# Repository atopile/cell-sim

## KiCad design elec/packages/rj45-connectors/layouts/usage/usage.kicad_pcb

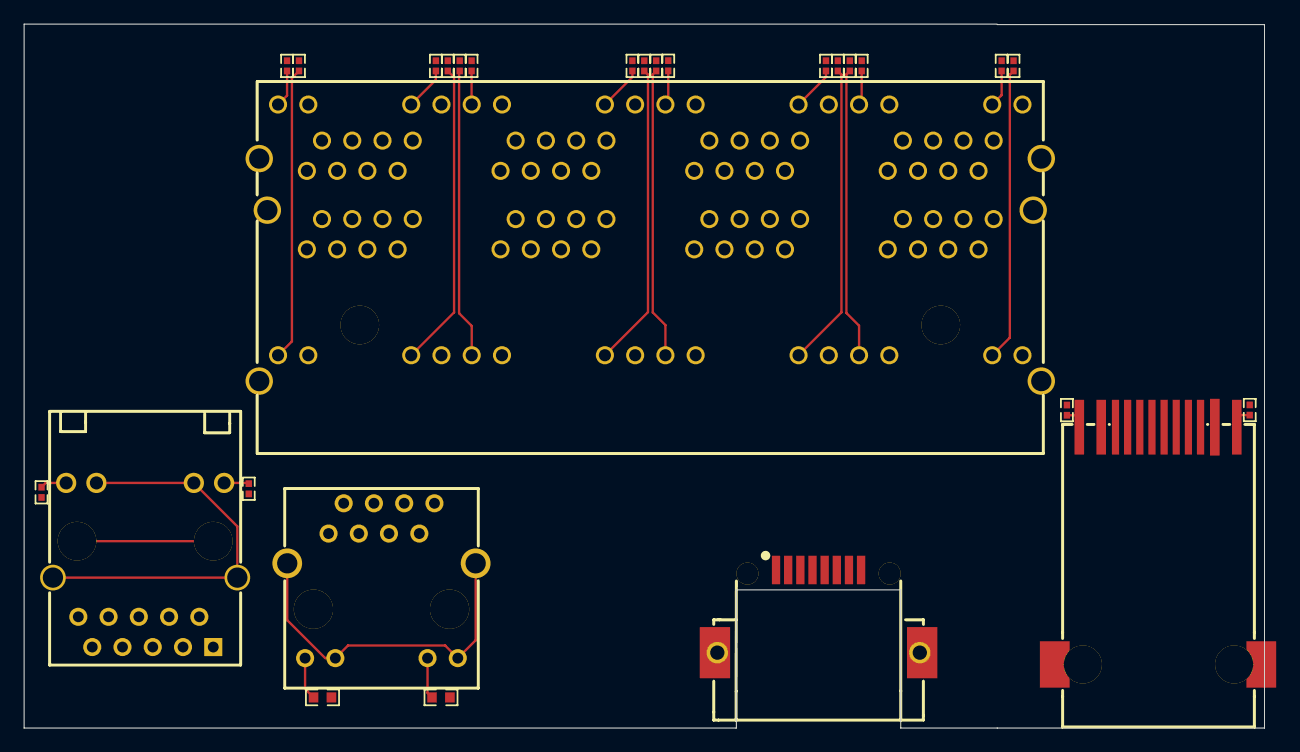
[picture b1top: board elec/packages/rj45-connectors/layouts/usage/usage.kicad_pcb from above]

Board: 2 copper layers, 104.1 x 59.1 mm, 27 parts (0 on the bottom side), 24 nets.

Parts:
R1, R2, R5, R6, R7, R8, R9, R10, R11, R12, R13, R14, R15, R16, R17, R18, R19, R20, R21, R22: 470Ω; R0402
R3, R4: 10kΩ; R0603
RJ1: RJ45-TH_HR911130A
RJ2: RJ45-SMD_BS-R250210
U1: RJ45-TH_R-RJ45S08P-C000
U2: RJ45-SMD_HC-RJ45-055-7_1
U3: RJ45-TH_HC-RJ45-059C-2X4-1

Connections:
10: R13.2, U3.10
11: R2.2, RJ1.11
12: R5.2, U3.12
14: R1.2, RJ1.14
22: R14.2, U3.22
24: R6.2, U3.24
34: R15.2, U3.34
36: R7.2, U3.36
46: R16.2, U3.46
48: R8.2, U3.48
57: R9.2, U3.57
59: R17.2, U3.59
69: R10.2, U3.69
71: R18.2, U3.71
81: R11.2, U3.81
83: R19.2, U3.83
93: R12.2, U3.93
95: R20.2, U3.95
CT: RJ2.3, RJ2.4
Gpos: R4.2, U1.11
L_LED_Gpos: R22.2, RJ2.12
R_LEDYpos: R21.2, RJ2.9
Ypos: R3.2, U1.9
lv: RJ1.12, RJ1.13, RJ1.SHIELD0, RJ1.SHIELD1, RJ2.8, RJ2.10, RJ2.11, RJ2.13, RJ2.14, U1.10, U1.12, U1.13, U1.14, U2.9, U2.10, U3.9, U3.11, U3.21, U3.23, U3.33, U3.35, U3.45, U3.47, U3.58, U3.60, U3.70, U3.72, U3.82, U3.84, U3.94, U3.96, U3.97, U3.98, U3.99, U3.100, U3.101, U3.102

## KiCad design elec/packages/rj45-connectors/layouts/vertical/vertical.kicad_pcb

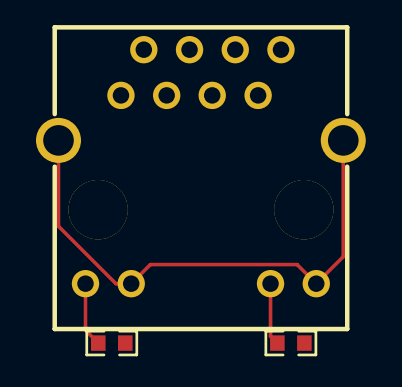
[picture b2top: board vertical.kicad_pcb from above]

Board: 2 copper layers, 3 parts (0 on the bottom side), 3 nets.

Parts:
R1, R2: 10kΩ; R0603
RJ1: RJ45-TH_R-RJ45S08P-C000

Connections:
Gpos: R2.2, RJ1.11
Ypos: R1.2, RJ1.9
lv: RJ1.10, RJ1.12, RJ1.13, RJ1.14

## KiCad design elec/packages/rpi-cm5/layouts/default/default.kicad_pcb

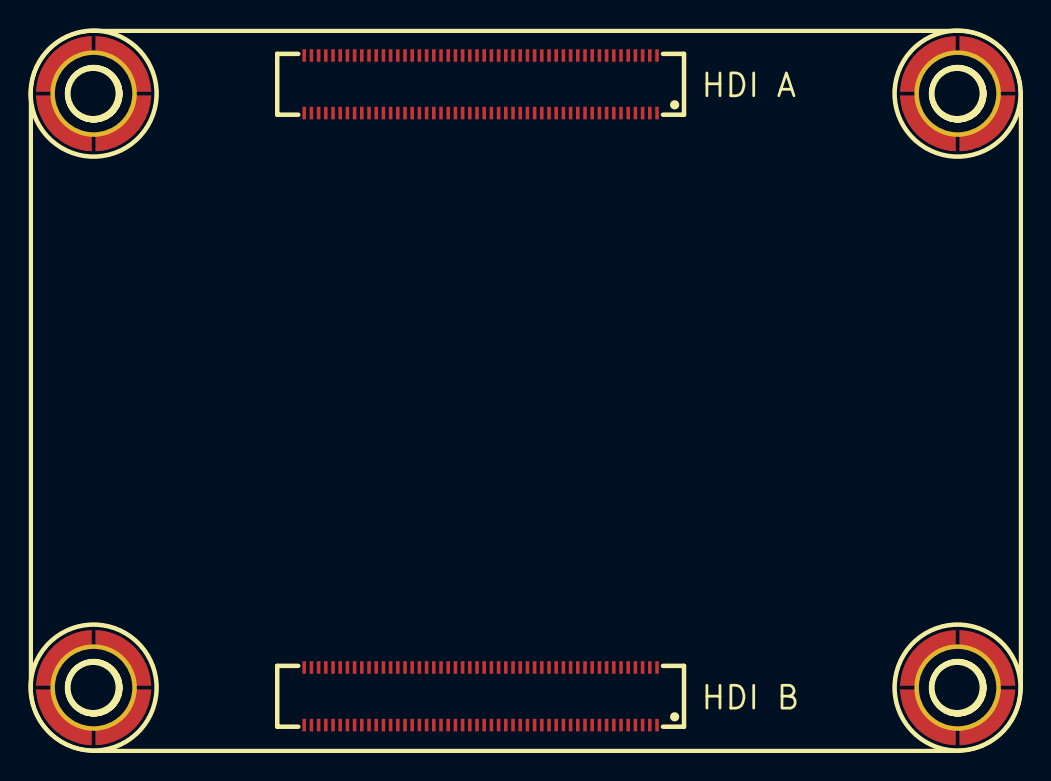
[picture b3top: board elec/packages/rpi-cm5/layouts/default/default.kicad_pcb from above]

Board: 4 copper layers, 7 parts (0 on the bottom side), 5 nets, no tracks yet.

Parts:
CN1, CN2: CONN-SMD_DF40C-100DS-0.4V-51
U1, U2, U3, U4: SMD_BD5.6-D4.1
U5: cm5

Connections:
lv: CN1.1, CN1.4, CN1.7, CN1.11, CN1.16, CN1.21, CN1.26, CN1.30, CN1.33, CN1.37, CN1.49, CN1.65, CN1.68, CN1.71, CN1.74, CN1.79, CN1.84, CN1.89, CN1.94, CN1.97, CN1.100, CN2.4, CN2.7, CN2.10, CN2.13, CN2.16, CN2.22, CN2.28, CN2.31, CN2.34, CN2.37, CN2.40, CN2.43, CN2.46, CN2.49, CN2.52, CN2.55, CN2.58, CN2.61, CN2.64, CN2.67, CN2.70, CN2.73, CN2.82, CN2.85, CN2.88, CN2.91, CN2.94, CN2.97
power_1v8-hv: CN1.44, CN1.45
power_3v3-hv: CN1.42, CN1.43
power_3v3-lv: U1.1, U1.2, U1.3, U1.4, U1.5, U2.1, U2.2, U2.3, U2.4, U2.5, U3.1, U3.2, U3.3, U3.4, U3.5, U4.1, U4.2, U4.3, U4.4, U4.5
power_5v-hv: CN1.57, CN1.58, CN1.59, CN1.60, CN1.61, CN1.62

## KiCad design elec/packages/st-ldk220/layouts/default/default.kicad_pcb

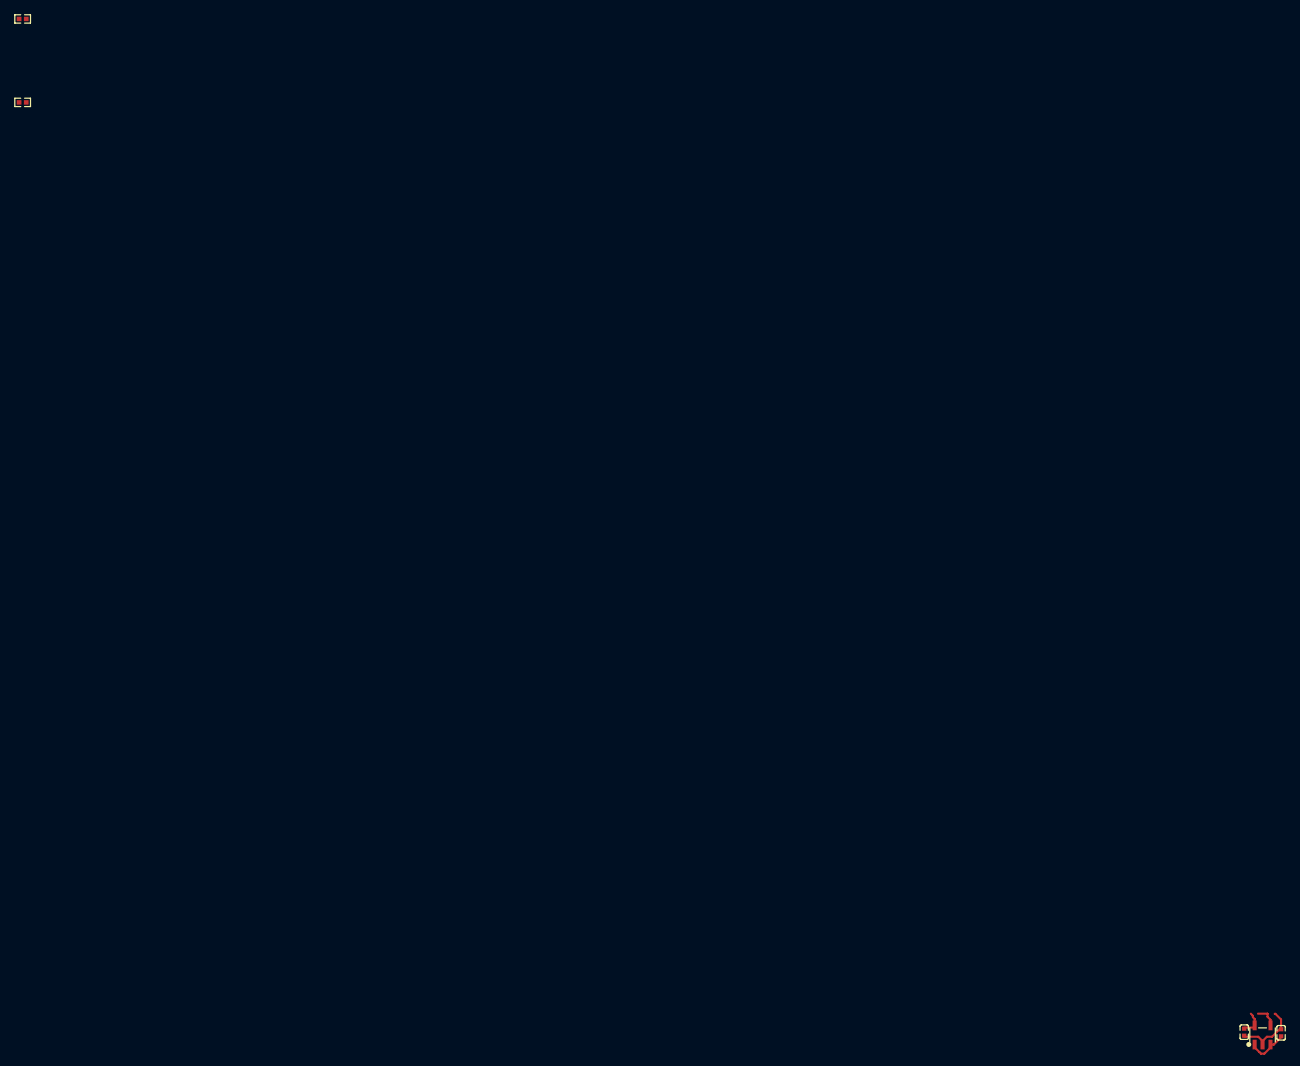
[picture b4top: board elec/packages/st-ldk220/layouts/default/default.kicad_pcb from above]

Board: 2 copper layers, 5 parts (0 on the bottom side), 5 nets.

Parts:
C1, C2: 1µF; C0402
R1, R2: 10kΩ; R0402
U1: SOT-23-5_L3.0-W1.7-P0.95-LS2.8-BL

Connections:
hv: C2.1, R1.1, U1.5
input_decoupling_capacitor-power-hv: C1.1, U1.1, U1.3
input_decoupling_capacitor-power-lv: C1.2, U1.2
lv: C2.2, R2.2
ref_out-hv: R1.2, R2.1, U1.4

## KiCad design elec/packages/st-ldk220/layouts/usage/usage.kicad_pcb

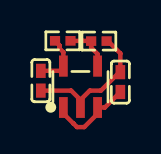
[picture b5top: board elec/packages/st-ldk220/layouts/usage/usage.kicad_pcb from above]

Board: 2 copper layers, 5 parts (0 on the bottom side), 4 nets.

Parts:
C1, C2: 1µF ±10% 25V X5R; C0402
R1: 5.1kΩ ±1% 62.5mW; R0402
R2: 10kΩ ±1% 62.5mW; R0402
U1: SOT-23-5_L3.0-W1.7-P0.95-LS2.8-BL

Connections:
GND: C1.2, C2.2, R1.2, U1.2
VDIV_OUTPUT: R1.1, R2.2, U1.4
power_in-VCC: C1.1, U1.1, U1.3
power_shim-VCC: C2.1, R2.1, U1.5

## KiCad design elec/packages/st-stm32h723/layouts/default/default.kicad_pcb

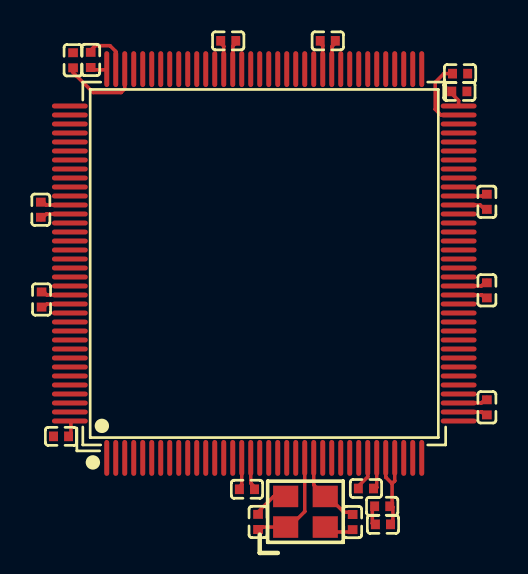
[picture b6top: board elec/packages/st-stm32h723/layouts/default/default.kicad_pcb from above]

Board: 2 copper layers, 20 parts (0 on the bottom side), 5 nets.

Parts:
C1, C2, C3, C4, C5, C6, C7, C8, C13, C14, C15, C16, C18: 100nF; C0402
C9, C10: 18pF; C0402
C11, C12: 2.2µF; C0402
C17: 1µF; C0402
U1: LQFP-144_L20.0-W20.0-P0.50-LS22.0-BL
X1: OSC-SMD_4P-L3.2-W2.5-BL_SIT8008BI

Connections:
XIN: C9.1, U1.23, X1.1
XOUT: C10.1, U1.24, X1.3
hv: C1.1, C2.1, C3.1, C4.1, C5.1, C6.1, C7.1, C8.1, C13.1, C14.1, C15.1, C16.1, C17.1, C18.1, U1.17, U1.30, U1.32, U1.33, U1.39, U1.52, U1.62, U1.72, U1.84, U1.95, U1.108, U1.121, U1.131, U1.144
lv: C1.2, C2.2, C3.2, C4.2, C5.2, C6.2, C7.2, C8.2, C9.2, C10.2, C11.2, C12.2, C13.2, C14.2, C15.2, C16.2, C17.2, C18.2, U1.16, U1.31, U1.38, U1.51, U1.61, U1.83, U1.94, U1.107, U1.120, U1.130, X1.2, X1.4
vcap_caps[1]-power-hv: C11.1, C12.1, U1.71, U1.106
